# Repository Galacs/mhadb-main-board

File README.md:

# MHADB Main board

ESP32-S3 Mhadb line follower main pcb with can interfaces and integrated BMS and 5b buck converter

## IC List

- ESP32-S3-WROOM
- LDL212 (3v3 LDO)
- BQ77905 (3S battery protection)
- TPS56A37 (5v smps)
- SN65HVD (CAN transceiver)
- TMP117 (I2C temperature sensor)

## Related repositories

- [Galacs/mhadb-2208-bldc-drv](https://github.com/Galacs/mhadb-2208-bldc-drv)
- [Galacs/mhadb-line-sensor](https://github.com/Galacs/mhadb-line-sensor)
- [Galacs/mhadb-firmware](https://github.com/Galacs/mhadb-firmware)

## Top preview

## Preview 3d render

## Pictures

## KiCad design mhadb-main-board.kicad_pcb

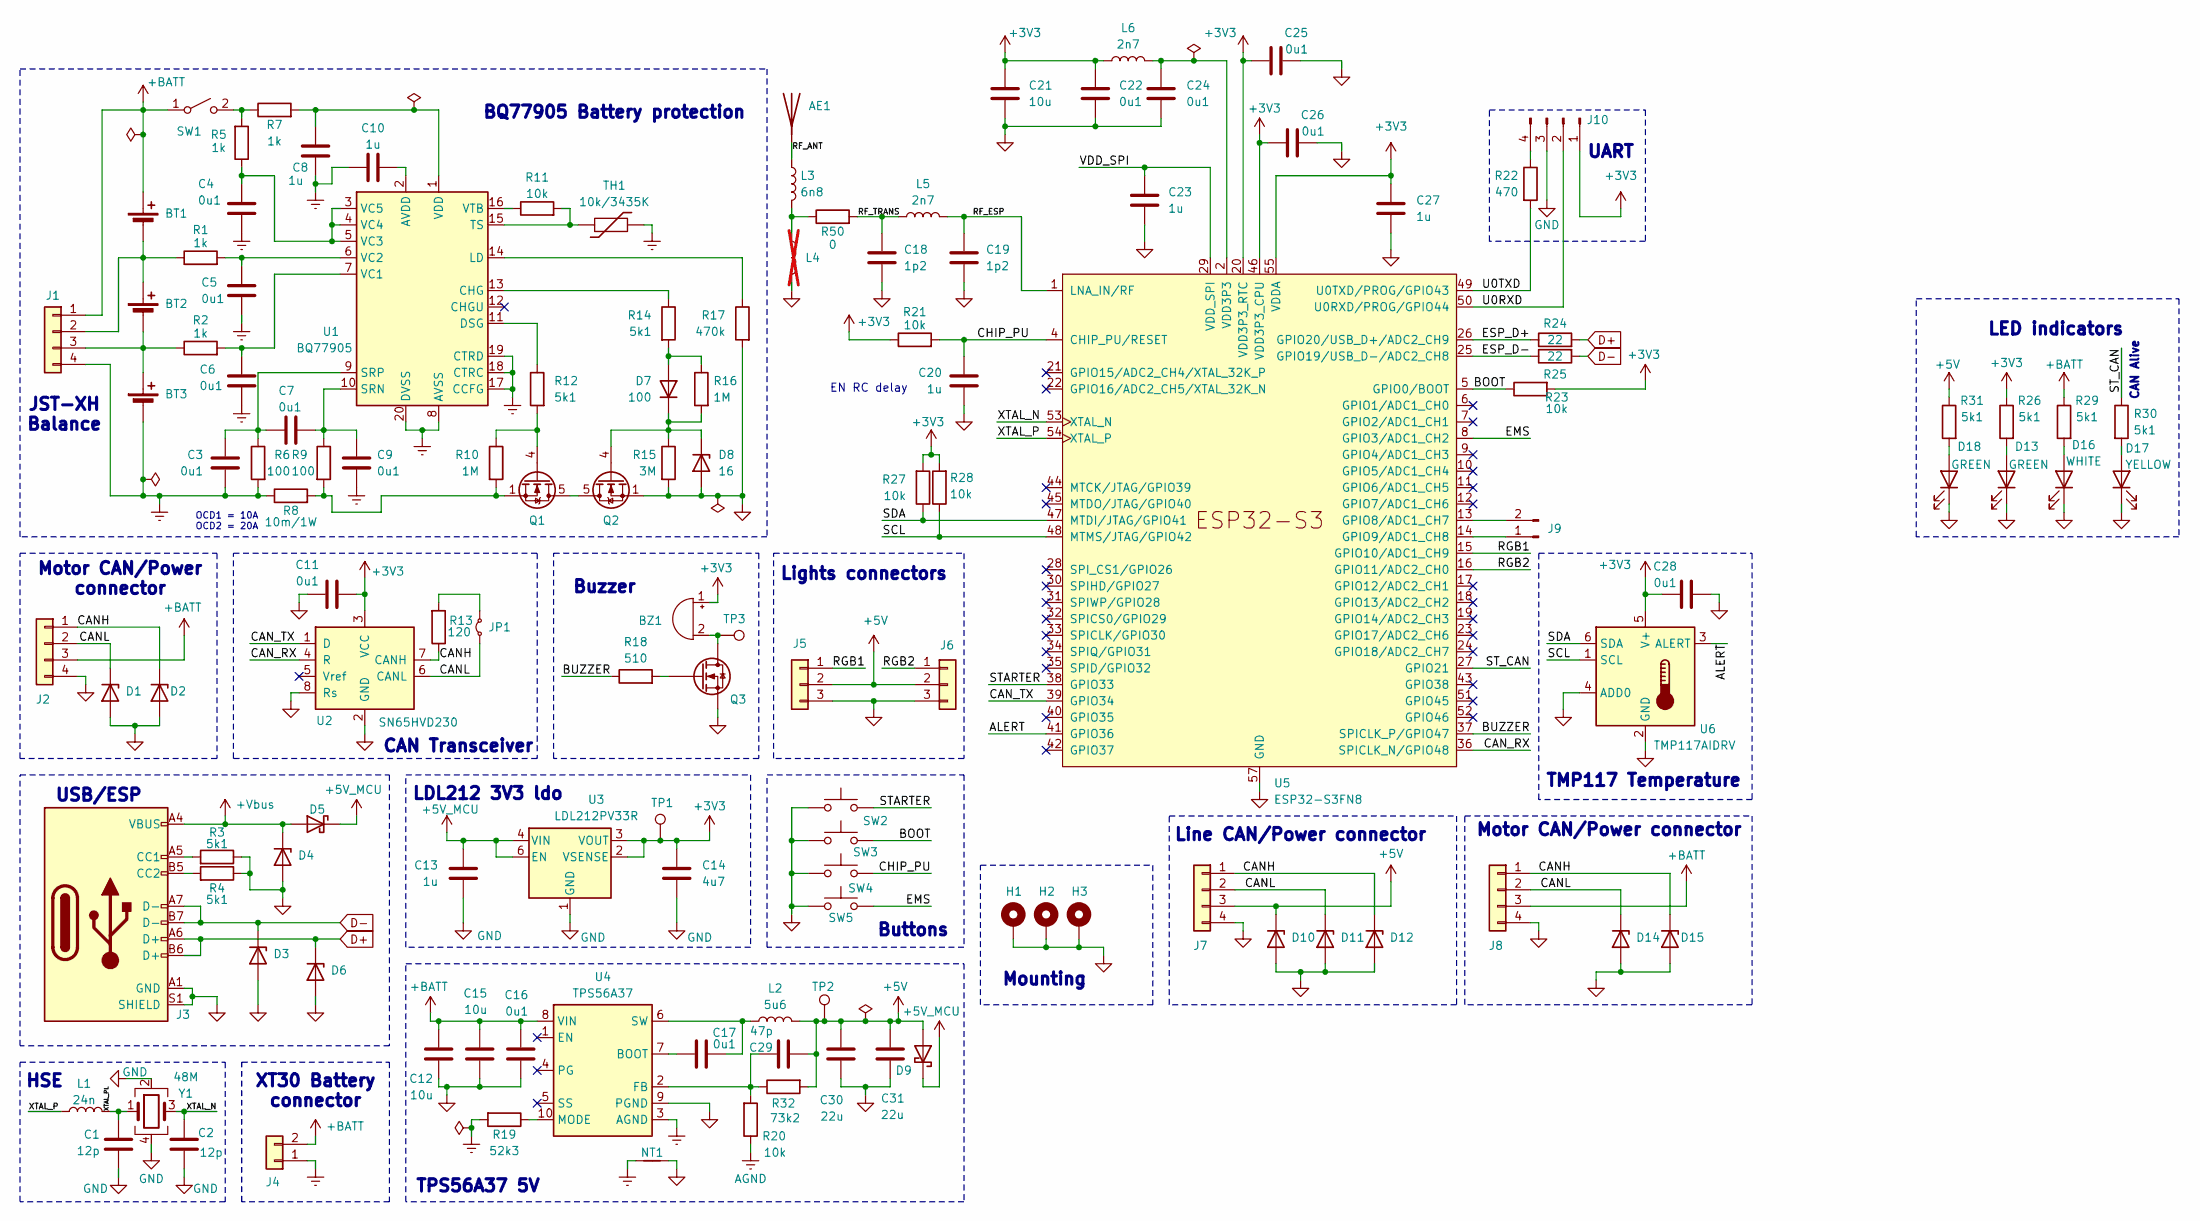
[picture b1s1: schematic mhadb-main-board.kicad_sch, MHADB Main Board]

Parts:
AE1: Antenna; Johanson_2450AT18x100; Manufacturer Part Number RFANT3216120A5T; JLCPCB Part # C127629
BT1, BT2, BT3: Battery_Cell; BatteryHolder_MYOUNG_BH-18650-B1BA002
BZ1: Buzzer; MagneticBuzzer_Huaneng_MLT-5020; Manufacturer Part Number MLT-5020; JLCPCB Part # C94598
C1, C2: 12p; C_0402_1005Metric; Manufacturer Part Number 0402CG120J500NT; JLCPCB Part # C1547
C3, C4, C5, C6, C7, C9, C11, C16, C17, C22, C24, C25, C26, C28: 0u1; C_0402_1005Metric; Manufacturer Part Number CL05B104KB54PNC; JLCPCB Part # C307331
C8, C10, C13, C20, C23, C27: 1u; C_0402_1005Metric; Manufacturer Part Number CL05A105KA5NQNC; JLCPCB Part # C52923
C12, C15: 10u; C_0805_2012Metric; Manufacturer Part Number GRM21BR61H106KE43L; JLCPCB Part # C440198
C14: 4u7; C_0402_1005Metric; Manufacturer Part Number CL05A475MP5NRNC; JLCPCB Part # C23733
C18, C19: 1p2; C_0402_1005Metric; Manufacturer Part Number GJM1555C1H1R2WB01D; JLCPCB Part # C76899
C21: 10u; C_0402_1005Metric; Manufacturer Part Number CL05A106MQ5NUNC; JLCPCB Part # C15525
C29: 47p; C_0402_1005Metric; Manufacturer Part Number 0402CG470J500NT; JLCPCB Part # C1567
C30, C31: 22u; C_0805_2012Metric; Manufacturer Part Number CL21A226MAQNNNE; JLCPCB Part # C45783
D1, D2, D3, D4, D6, D10, D11, D12, D14, D15: H5VU10U; Diode_DFN1006; Manufacturer Part Number H5VU10U; JLCPCB Part # C22395519
D5, D9: D_Schottky; D_SMA; Manufacturer Part Number SS54; JLCPCB Part # C22452
D7: 100; D_SOD-323; Manufacturer Part Number 1N4148WS; JLCPCB Part # C2128
D8: 16; D_SOD-123; Manufacturer Part Number MMSZ5246B; JLCPCB Part # C19077429
D13, D18: GREEN; LED_0805_2012Metric; Manufacturer Part Number KT-0805G; JLCPCB Part # C2297
D16: WHITE; LED_0603_1608Metric; Manufacturer Part Number KT-0603W; JLCPCB Part # C2290
D17: YELLOW; LED_0805_2012Metric; Manufacturer Part Number KT-0805Y; JLCPCB Part # C2296
H1, H2, H3: MountingHole_Pad; MountingHole_3.2mm_M3_DIN965_Pad_Thin
J1, J2, J8: Conn_01x04; JST_XH_B4B-XH-A_1x04_P2.50mm_Vertical; Manufacturer Part Number B4B-XH-A(LF)(SN); JLCPCB Part # C144395
J3: USB_C_Receptacle_USB2.0_14P; USB_C_Receptacle_HRO_TYPE-C-31-M-12; Manufacturer Part Number TYPE-C16PIN; JLCPCB Part # C393939
J4: Conn_01x02; AMASS_XT30U-M_1x02_P5.0mm_Vertical; Manufacturer Part Number XT30U-M; JLCPCB Part # C99101
J5, J6: Conn_01x03; JST_PH_B3B-PH-K_1x03_P2.00mm_Vertical; Manufacturer Part Number B3B-PH-K-S(LF)(SN); JLCPCB Part # C131339
J7: Conn_01x04; JST_PH_S4B-PH-K_1x04_P2.00mm_Horizontal; Manufacturer Part Number S4B-PH-K-S(LF)(SN); JLCPCB Part # C157926
J9: Conn_01x02_Pin; PinHeader_1x02_P2.54mm_Vertical
J10: Conn_01x04_Pin; PinHeader_1x04_P2.54mm_Vertical
JP1: Jumper_2_Small_Bridged; SolderJumper-2_P1.3mm_Open_RoundedPad1.0x1.5mm
L1: 24n; L_0402_1005Metric; Manufacturer Part Number LQW15AN24NG00D; JLCPCB Part # C167472
L2: 5u6; L_10.4x10.4_H4.8; Manufacturer Part Number DH1040H-5R6M; JLCPCB Part # C41407183
L3: 6n8; L_0402_1005Metric; Manufacturer Part Number LQG15HS6N8J02D; JLCPCB Part # C77110
L4: L; L_0402_1005Metric; not fitted
L5, L6: 2n7; L_0402_1005Metric; Manufacturer Part Number LQG15HS2N7S02D; JLCPCB Part # C77108
NT1: NetTie_2; NetTie-2_SMD_Pad0.5mm
Q1, Q2: Q_NMOS; Vishay_PowerPAK_1212-8_Single; Manufacturer Part Number SIS412DN-T1-GE3; JLCPCB Part # C111309
Q3: Q_NMOS; SOT-323_SC-70; Manufacturer Part Number BSS138W; JLCPCB Part # C28646265
R1, R2, R5, R7: 1k; R_0402_1005Metric; Manufacturer Part Number 0402WGF1001TCE; JLCPCB Part # C11702
R3, R4, R12, R14, R26, R29, R30, R31: 5k1; R_0402_1005Metric; Manufacturer Part Number 0402WGF5101TCE; JLCPCB Part # C25905
R6, R9: 100; R_0402_1005Metric; Manufacturer Part Number 0402WGF1000TCE; JLCPCB Part # C25076
R8: 10m/1W; R_1206_3216Metric; Manufacturer Part Number FMF06FTHR010-LH; JLCPCB Part # C105362
R10, R16: 1M; R_0402_1005Metric; Manufacturer Part Number 0402WGF1004TCE; JLCPCB Part # C26083
R11, R20, R21, R23, R27, R28: 10k; R_0402_1005Metric; Manufacturer Part Number 0402WGF1002TCE; JLCPCB Part # C25744
R13: 120; R_1206_3216Metric; Manufacturer Part Number 1206W4F1200T5E; JLCPCB Part # C17909
R15: 3M; R_0603_1608Metric; Manufacturer Part Number 0603WAF3004T5E; JLCPCB Part # C23156
R17: 470k; R_0603_1608Metric; Manufacturer Part Number 0603WAF4703T5E; JLCPCB Part # C23178
R18: 510; R_0402_1005Metric; Manufacturer Part Number 0402WGF5100TCE; JLCPCB Part # C25123
R19: 52k3; R_0402_1005Metric; Manufacturer Part Number 0402WGF5232TCE; JLCPCB Part # C26982
R22: 470; R_0402_1005Metric; Manufacturer Part Number 0402WGF4700TCE; JLCPCB Part # C25117
R24, R25: 22; R_0402_1005Metric; Manufacturer Part Number 0402WGF220JTCE; JLCPCB Part # C25092
R32: 73k2; R_0402_1005Metric; Manufacturer Part Number 0402WGF7322TCE; JLCPCB Part # C26986
R50: 0; R_0402_1005Metric; Manufacturer Part Number 0402WGF0000TCE; JLCPCB Part # C17168
SW1: SW_SPST; PinHeader_1x02_P2.54mm_Vertical
SW2: SW_Push; PinHeader_1x02_P2.54mm_Vertical
SW3, SW4: SW_Push; SW_SPST_TS-1088-xR020; Manufacturer Part Number TS-1088-AR02016; JLCPCB Part # C720477
SW5: SW_Push; JST_PH_B2B-PH-K_1x02_P2.00mm_Vertical; Manufacturer Part Number B2B-PH-K-S(LF)(SN); JLCPCB Part # C131337
TH1: 10k/3435K; JST_PH_B2B-PH-K_1x02_P2.00mm_Vertical; Manufacturer Part Number B2B-PH-K-S(LF)(SN); JLCPCB Part # C131337
TP1, TP2, TP3: TestPoint; TestPoint_Pad_D2.0mm
U1: BQ77905; TSSOP-20_4.4x6.5mm_P0.65mm; Manufacturer Part Number BQ7790509PWR; JLCPCB Part # C2866527
U2: SN65HVD230; SOIC-8_3.9x4.9mm_P1.27mm; Manufacturer Part Number SN65HVD230DR; JLCPCB Part # C12084
U3: LDL212PV33R; DFN-6-1EP_2x2mm_P0.5mm_ST; Manufacturer Part Number LDL212PV33R; JLCPCB Part # C2969892
U4: TPS56A37; Texas_RPA0010A_VQFN-HR-10_3x3mm_P0.5mm; Manufacturer Part Number TPS56A37RPAR; JLCPCB Part # C22392669
U5: ESP32-S3FN8; QFN-56-1EP_7x7mm_P0.4mm_EP4x4mm_ThermalVias; Manufacturer Part Number ESP32-S3FH4R2; JLCPCB Part # C3013940
U6: TMP117AIDRV; WSON-6-1EP_2x2mm_P0.65mm_EP1x1.6mm; Manufacturer Part Number TMP117AIDRVR; JLCPCB Part # C699536
Y1: 48M; Crystal_SMD_2016-4Pin_2.0x1.6mm; Manufacturer Part Number R940000096; JLCPCB Part # C7206306

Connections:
+3V3: BZ1.1 (+), C11.1, C14.1, C21.1, C22.1, C25.1, C26.1, C27.1, C28.1, J10.1, L6.1, R21.1, R23.2, R26.1, R27.2, R28.2, TP1.1, U2.3 (VCC), U3.2 (VSENSE), U3.3 (VOUT), U5.20 (VDD3P3_RTC), U5.46 (VDD3P3_CPU), U5.55 (VDDA), U5.56 (VDDA), U6.5 (V+)
+5V: C29.2, C30.1, C31.1, D9.2 (A), D10.1 (K), J5.2, J6.2, J7.3, L2.2, R31.1, R32.2, TP2.1
+5V_MCU: C13.1, D5.1 (K), D9.1 (K), U3.4 (VIN), U3.6 (EN)
+BATT: BT1.1 (+), C12.1, C15.1, C16.1, J1.1, J2.3, J4.2, J8.3, R29.1, SW1.1 (A), U4.8 (VIN)
+Vbus: D4.1 (K), D5.2 (A), J3.A4 (VBUS), J3.A9 (VBUS), J3.B4 (VBUS), J3.B9 (VBUS)
/ALERT: U5.41 (GPIO36), U6.3 (ALERT)
/BOOT: R23.1, SW3.2, U5.5 (GPIO0/BOOT)
/BUZZER: R18.1, U5.37 (SPICLK_P/GPIO47)
/CANH: D2.1 (K), D12.1 (K), D15.1 (K), J2.1, J7.1, J8.1, R13.1, U2.7 (CANH)
/CANL: D1.1 (K), D11.1 (K), D14.1 (K), J2.2, J7.2, J8.2, JP1.1 (A), U2.6 (CANL)
/CAN_RX: U2.4 (R), U5.36 (SPICLK_N/GPIO48)
/CAN_TX: U2.1 (D), U5.39 (GPIO34)
/CHIP_PU: C20.1, R21.2, SW4.2, U5.4 (CHIP_PU/RESET)
/EMS: SW5.2, U5.8 (GPIO3/ADC1_CH2)
/ESP_D+: R24.1, U5.26 (GPIO20/USB_D+/ADC2_CH9)
/ESP_D-: R25.1, U5.25 (GPIO19/USB_D-/ADC2_CH8)
/RF_ANT: AE1.1 (A), L3.1
/RF_ESP: C19.1, L5.2, U5.1 (LNA_IN/RF)
/RF_TRANS: C18.1, L5.1, R50.2
/RGB1: J5.1, U5.15 (GPIO10/ADC1_CH9)
/RGB2: J6.1, U5.16 (GPIO11/ADC2_CH0)
/SCL: R28.1, U5.48 (MTMS/JTAG/GPIO42), U6.1 (SCL)
/SDA: R27.1, U5.47 (MTDI/JTAG/GPIO41), U6.6 (SDA)
/STARTER: SW2.2, U5.38 (GPIO33)
/ST_CAN: R30.1, U5.27 (GPIO21)
/U0RXD: J10.2, U5.50 (U0RXD/PROG/GPIO44)
/U0TXD: R22.2, U5.49 (U0TXD/PROG/GPIO43)
/VDD_SPI: C23.1, U5.29 (VDD_SPI)
/XTAL_N: C2.1, U5.53 (XTAL_N), Y1.3
/XTAL_P: L1.1, U5.54 (XTAL_P)
/XTAL_PL: C1.2, L1.2, Y1.1
AGND: NT1.1, R19.2, R20.1, U4.3 (AGND)
BGND: BT3.2 (-), C3.2, C4.2, C5.2, C6.2, C8.1, C9.2, C10.2, J1.4, J4.1, R6.2, R8.1, TH1.2, U1.8 (AVSS), U1.17 (CCFG), U1.18 (CTRC), U1.19 (CTRD), U1.20 (DVSS)
D+: D6.1 (K), J3.A6 (D+), J3.B6 (D+), R24.2
D-: D3.1 (K), J3.A7 (D-), J3.B7 (D-), R25.2
GND: C1.1, C2.2, C11.2, C12.2, C13.2, C14.2, C15.2, C16.2, C18.2, C19.2, C20.2, C21.2, C22.2, C23.2, C24.2, C25.2, C26.2, C27.2, C28.2, C30.2, C31.2, D1.2 (A), D2.2 (A), D3.2 (A), D4.2 (A), D6.2 (A), D8.2 (A), D10.2 (A), D11.2 (A), D12.2 (A), D13.1 (K), D14.2 (A), D15.2 (A), D16.1 (K), D17.1 (K), D18.1 (K), H1.1, H2.1, H3.1, J2.4, J3.A1 (GND), J3.A12 (GND), J3.B1 (GND), J3.B12 (GND), J3.S1 (SHIELD), J5.3, J6.3, J7.4, J8.4, J10.3, L4.2, NT1.2, Q2.1 (S), Q2.2 (S), Q2.3 (S), Q3.2 (S), R3.1, R4.1, R15.2, R17.2, SW2.1, SW3.1, SW4.1, SW5.1, U2.2 (GND), U2.8 (Rs), U3.1 (GND), U4.9 (PGND), U5.57 (GND), U6.2 (GND), U6.4 (ADD0), U6.7, Y1.2, Y1.4
unnamed: BZ1.2 (-), Q3.3 (D), TP3.1
unnamed: D7.2 (A), R14.2, R16.1
unnamed: D7.1 (K), D8.1 (K), Q2.4 (G), R15.1, R16.2
unnamed: D13.2 (A), R26.2
unnamed: D16.2 (A), R29.2
unnamed: D17.2 (A), R30.2
unnamed: D18.2 (A), R31.2
unnamed: BT1.2 (-), BT2.1 (+), J1.2, R1.1
unnamed: BT2.2 (-), BT3.1 (+), J1.3, R2.1
unnamed: J3.A5 (CC1), R3.2
unnamed: J3.B5 (CC2), R4.2
unnamed: J9.1, U5.14 (GPIO9/ADC1_CH8)
unnamed: J9.2, U5.13 (GPIO8/ADC1_CH7)
unnamed: J10.4, R22.1
unnamed: JP1.2 (B), R13.2
unnamed: L3.2, L4.1, R50.1
unnamed: Q1.5 (D), Q2.5 (D)
unnamed: Q1.4 (G), R10.1, R12.2
unnamed: Q1.1 (S), Q1.2 (S), Q1.3 (S), R8.2, R9.2, R10.2
unnamed: Q3.1 (G), R18.2
unnamed: R5.2, R7.1, SW1.2 (B)
unnamed: C10.1, U1.2 (AVDD)
unnamed: R14.1, U1.13 (CHG)
unnamed: R12.1, U1.11 (DSG)
unnamed: R17.1, U1.14 (LD)
unnamed: C7.1, C9.1, R9.1, U1.10 (SRN)
unnamed: C3.1, C7.2, R6.1, U1.9 (SRP)
unnamed: R11.2, TH1.1, U1.15 (TS)
unnamed: C6.1, R2.2, U1.7 (VC1)
unnamed: C5.1, R1.2, U1.6 (VC2)
unnamed: C4.1, R5.1, U1.3 (VC5), U1.4 (VC4), U1.5 (VC3)
unnamed: C8.2, R7.2, U1.1 (VDD)
unnamed: R11.1, U1.16 (VTB)
unnamed: C17.1, U4.7 (BOOT)
unnamed: C29.1, R20.2, R32.1, U4.2 (FB)
unnamed: R19.1, U4.10 (MODE)
unnamed: C17.2, L2.1, U4.6 (SW)
VDD3P3: C24.1, L6.2, U5.2 (VDD3P3), U5.3 (VDD3P3)

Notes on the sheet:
Motor CAN/Power connector
Buttons
XT30 Battery connector
TMP117 Temperature
Buzzer
USB/ESP
CAN Transceiver
HSE
JST-XH Balance
Lights connectors
LDL212 3V3 ldo
UART
BQ77905 Battery protection
TPS56A37 5V
OCD1 = 10A OCD2 = 20A
Mounting
Motor CAN/Power connector
Line CAN/Power connector
CAN Alive
EN RC delay
LED indicators

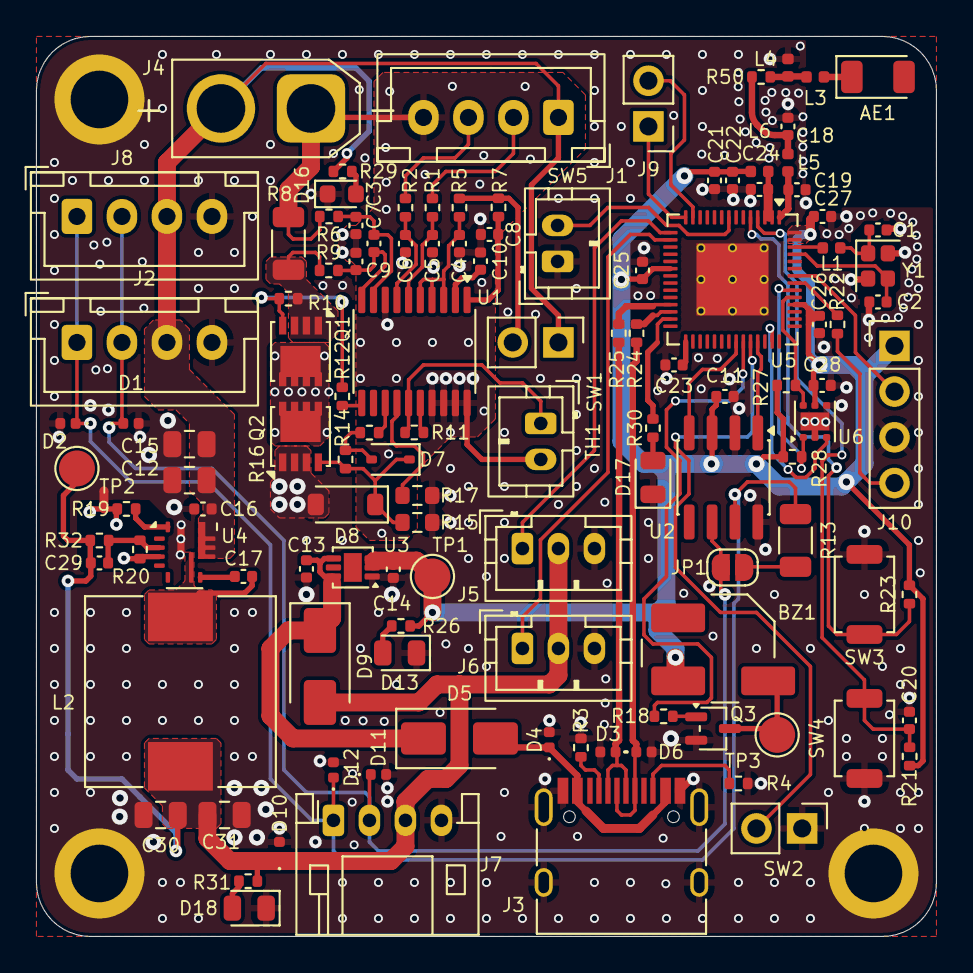
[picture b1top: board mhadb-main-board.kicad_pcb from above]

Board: 4 copper layers, 50.0 x 50.0 mm, 122 parts (0 on the bottom side), 74 nets.

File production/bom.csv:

Designator,Footprint,Quantity,Value,LCSC Part #
AE1,Johanson_2450AT18x100,1,Antenna,C127629
BZ1,MagneticBuzzer_Huaneng_MLT-5020,1,Buzzer,C94598
"C1, C2",0402,2,12p,C1547
"C10, C13, C20, C23, C27, C8",0402,6,1u,C52923
"C11, C22, C24, C25, C26, C28, C3, C4, C5, C6, C7, C9",0402,12,0u1,C307331
C12,0805,1,10u,C440198
C14,0402,1,4u7,C23733
C15,0402,1,10n,C15195
"C16, C17",1206,2,47u,C96123
"C18, C19",0402,2,1p2,C76899
C21,0402,1,10u,C15525
"D1, D10, D11, D12, D2, D3, D4, D6",Diode_DFN1006,8,H5VU10U,C22395519
"D13, D18",0805,2,GREEN,C2297
D16,0603,1,WHITE,C2290
D17,0805,1,YELLOW,C2296
D5,D_SMA,1,D_Schottky,C22452
D7,D_SOD-323,1,100,C2128
D8,D_SOD-123,1,16,C19077429
D9,D_SMA,1,SS34,C8678
J3,USB_C_Receptacle_HRO_TYPE-C-31-M-12,1,USB_C_Receptacle_USB2.0_14P,C393939
J4,AMASS_XT30U-M_1x02_P5.0mm_Vertical,1,Conn_01x02,C99101
"J5, J6",JST_PH_B3B-PH-K_1x03_P2.00mm_Vertical,2,Conn_01x03,C131339
J7,JST_PH_S4B-PH-K_1x04_P2.00mm_Horizontal,1,Conn_01x04,C157926
J9,PinHeader_1x02_P2.54mm_Vertical,1,Conn_01x02_Pin,
L1,0402,1,24n,C167472
L2,L_Sunlord_SWRB1207S,1,18u,C5161638
L3,0402,1,6n8,C77110
"Q1, Q2",Vishay_PowerPAK_1212-8_Single,2,Q_NMOS,C111309
Q3,SOT-323_SC-70,1,Q_NMOS,C28646265
"R1, R2, R5, R7",0402,4,1k,C11702
"R10, R16",0402,2,1M,C26083
"R11, R19, R21, R23, R27, R28",0402,6,10k,C25744
"R12, R14, R26, R29, R3, R30, R31, R4",0402,8,5k1,C25905
R13,1206,1,120,C17909
R15,0603,1,3M,C23156
R17,0603,1,470k,C23178
R18,0402,1,510,C25123
R20,0402,1,3k3,C25890
R22,0402,1,470,C25117
"R24, R25",0402,2,22,C25092
R50,0402,1,0,C17168
"R6, R9",0402,2,100,C25076
R8,1206,1,10m/1W,C105362
SW2,PinHeader_1x02_P2.54mm_Vertical,1,SW_Push,
"SW3, SW4",SW_SPST_TS-1088-xR020,2,SW_Push,C720477
SW5,JST_PH_B2B-PH-K_1x02_P2.00mm_Vertical,1,SW_Push,C131337
U1,TSSOP-20_4.4x6.5mm_P0.65mm,1,BQ77905,C2866527
U2,SOIC-8_3.9x4.9mm_P1.27mm,1,SN65HVD230,C12084
U3,DFN-6-1EP_2x2mm_P0.5mm_ST,1,LDL212PV33R,C2969892
U4,TI_SO-PowerPAD-8_ThermalVias,1,TPS5430DDA,C9864
U5,QFN-56-1EP_7x7mm_P0.4mm_EP4x4mm_ThermalVias,1,ESP32-S3FN8,C3013940
U6,WSON-6-1EP_2x2mm_P0.65mm_EP1x1.6mm,1,TMP117AIDRV,C699536
Y1,Crystal_SMD_2016-4Pin_2.0x1.6mm,1,48M,C7206306

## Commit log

2026-01-10 schem: import ESP32-S3FN8
2026-01-10 schem: import 2.4GHZ rf circuit
2026-01-10 schem: import reset circuit
2026-01-10 schem: import HSE oscilator
2026-01-10 schem: add BOOT pullup
2026-01-10 schem: import BOOT and CHIP_PU btns
2026-01-10 schem: add USB-C connector
2026-01-10 schem: import UART connector
2026-01-10 schem: import LDL212 3V3 LDO
2026-01-10 schem: add 2 motor can/power connector
2026-01-10 schem: add line can/power connector
2026-01-10 schem: import TPS5430 5v from motor-power-poc
2026-01-10 schem: add SN65HVD230 CAN Transceiver
2026-01-10 schem: add XT30 battery connector
2026-01-10 schem: import BQ77905 Battery protection
2026-01-10 schem: add passive buzzer
2026-01-10 schem: add EMS button
2026-01-10 schem: add starter connector
2026-01-11 schem: switch thermistor to 2 pin ph connector
2026-01-11 schem: add spare GPIIOs
2026-01-11 schem: add 2 JST PH 3 pin RGB led connectors
2026-01-11 schem: add no connects
2026-01-11 schem: add test points
2026-01-11 schem: switch pins for strapping
2026-01-11 schem: run and fix ERC
2026-01-11 schem: add net classes
2026-01-11 schem: add ESP32 to BOM
2026-01-11 schem: add title
2026-01-11 schem: renumber
2026-01-11 pcb: import stackup and constraints
2026-01-11 pcb: import components from schem
2026-01-11 pcb: add missing 3d models
2026-01-11 schem/pcb: fix XT30 polarity
2026-01-11 schem/pcb: changed esp32 footprint
2026-01-11 pcb: add board outline
2026-01-11 schem/pcb: add mounting holes
2026-01-11 pcb: refine layout of every block
2026-01-11 schem: remove extra testpoints
2026-01-11 pcb: initial layout
2026-01-11 schem/pcb: add TMP117 temp sensor
2026-01-11 pcb: changed outline to 50x50mm
2026-01-11 pcb: switched to 4 layer stackup
2026-01-11 pcb: add gnd planes
2026-01-11 pcb: add gnd vias
2026-01-11 pcb: add BMS BGND plane
2026-01-11 pcb: add BGND vias
2026-01-11 pcb: add grid/drill origin
2026-01-11 schem/pcb: reorganize GPIOs
2026-01-11 pcb: add RF routing
2026-01-11 pcb: add HSE crystal routing
2026-01-11 pcb: add USB routing
2026-01-11 pcb: add CAN routing
2026-01-11 pcb: add UART routing
2026-01-11 pcb: add SMPS routing
2026-01-11 pcb: add BQ77905 Battery protection routing
2026-01-11 pcb: add I2C routing
2026-01-11 pcb: add 5v pwr routing
2026-01-11 pcb: add 3V3 pwr routing
2026-01-11 pcb: add RGB connectors routing
2026-01-11 pcb: add spare GPIOs routing
2026-01-11 pcb: add buzzer routing
2026-01-11 pcb: add BOOT and CHIP_PU routing
2026-01-11 pcb: add EMS button routing
2026-01-11 pcb: add starter routing
2026-01-11 pcb: add missing connections
2026-01-11 pcb: add stitching vias
2026-01-11 pcb: run and fix DRC
2026-01-11 schem: reorganize
2026-01-11 pcb: remove unused internal pads
2026-01-11 pcb(silkscreen): clean reference designators
2026-01-11 schem/pcb: add status LEDs
2026-01-11 add production files
2026-01-11 pcb(silkscreen): replace placeholder
2026-01-11 schem: updated SMPS L BOM
2026-01-11 regenerate production files
2026-01-21 schem/pcb: remove TPS5430 5v SMPS
2026-01-21 schem/pcb: add TPS56A37 5V smps
2026-02-10 add README.md
2026-02-10 add related repo links to README.md
2026-02-10 docs: add pictures to README
